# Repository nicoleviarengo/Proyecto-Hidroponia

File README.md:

# Proyecto-Hidroponia
Primera version

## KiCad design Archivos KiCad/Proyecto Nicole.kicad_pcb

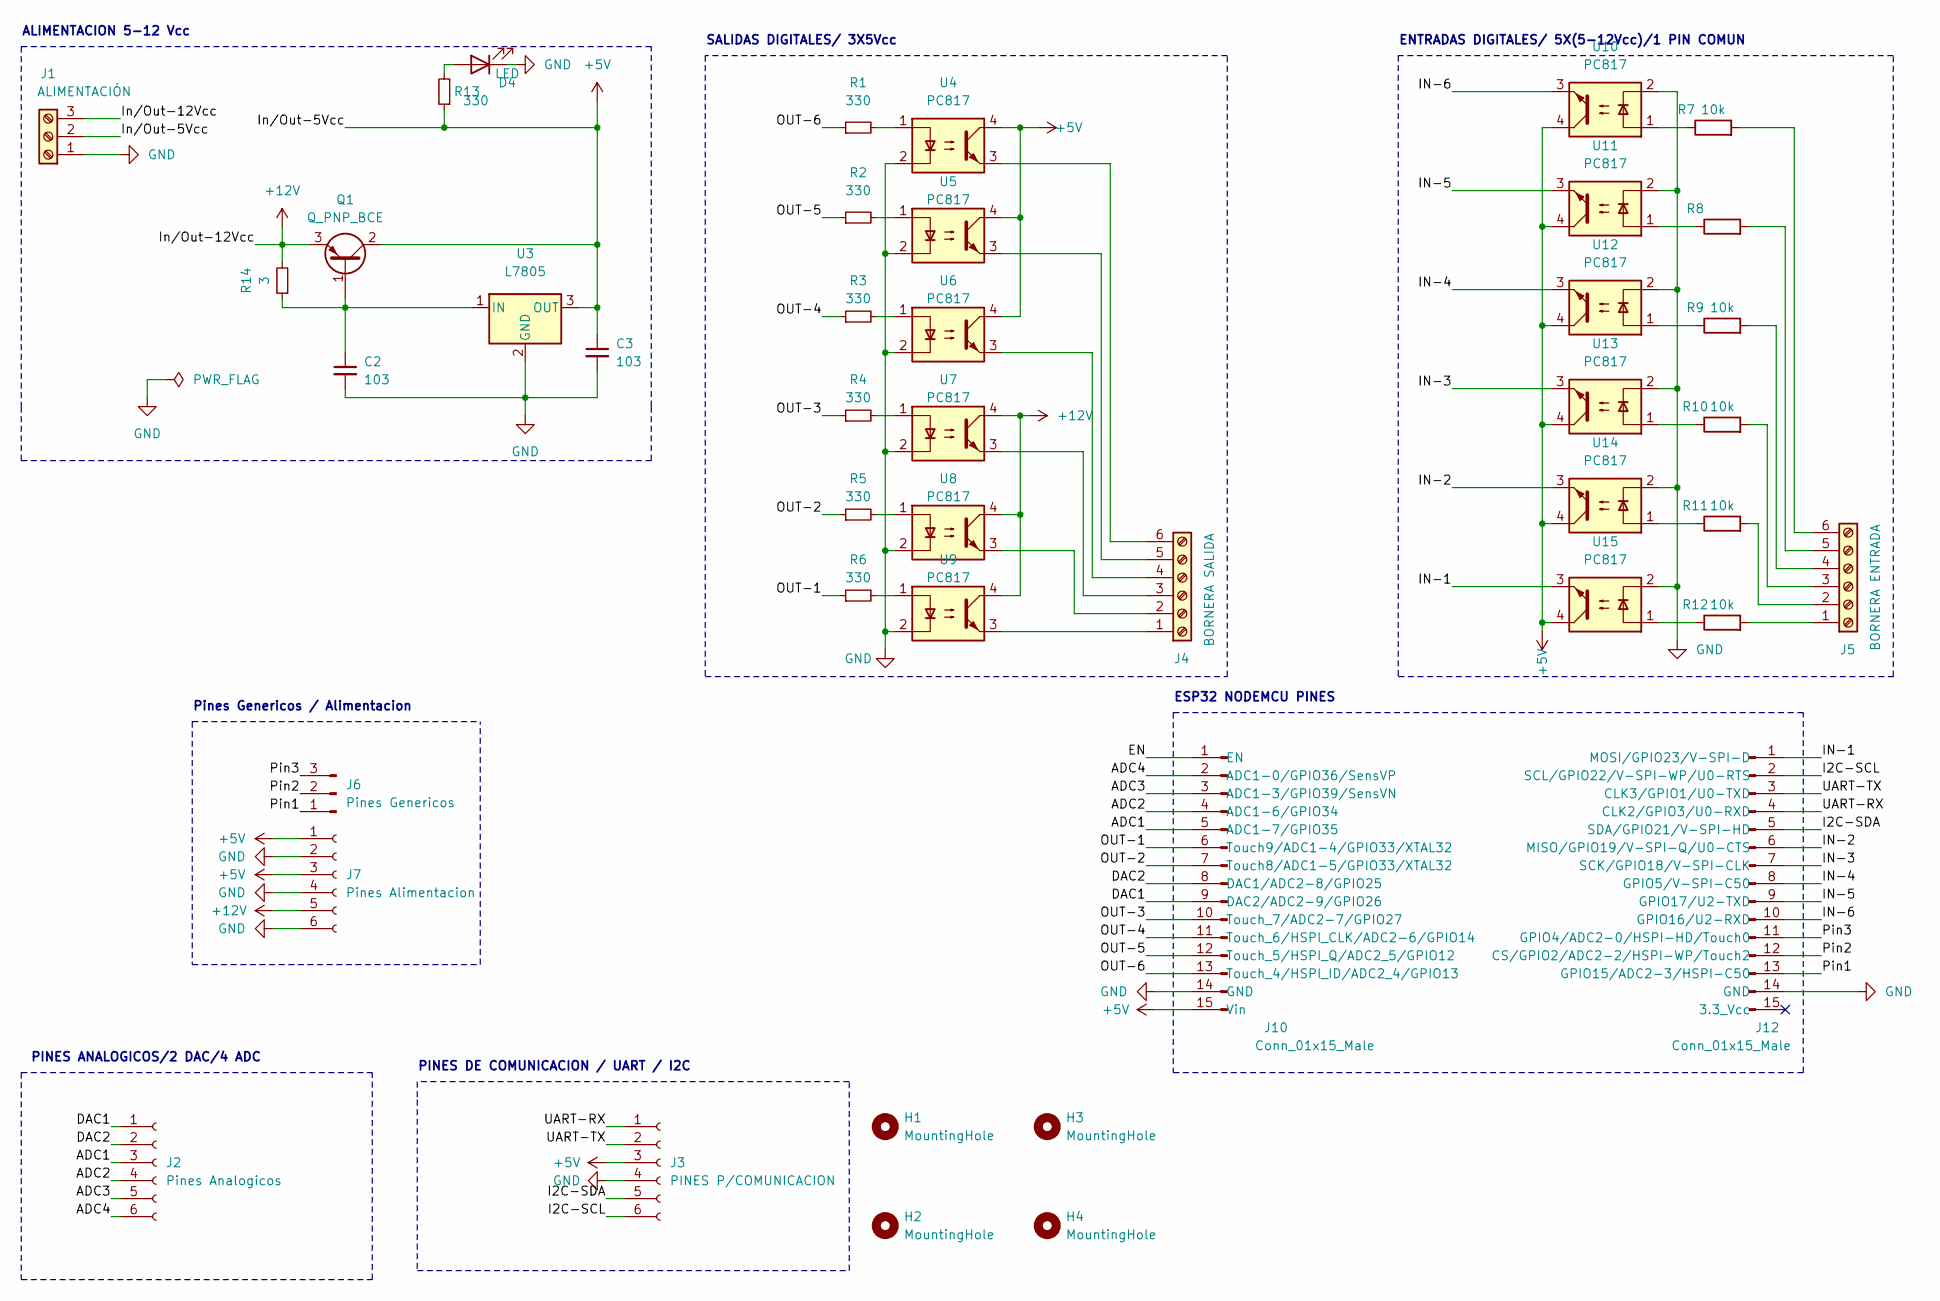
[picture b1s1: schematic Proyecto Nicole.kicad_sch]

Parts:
C2, C3: 103; C_Disc_D4.3mm_W1.9mm_P5.00mm
D4: LED; LED_D4.0mm
H1, H2, H3, H4: MountingHole; MountingHole_2.5mm_Pad
J1: ALIMENTACIÓN; TerminalBlock_Phoenix_MKDS-3-3-5.08_1x03_P5.08mm_Horizontal
J2: Pines Analogicos; PinSocket_1x06_P2.54mm_Vertical
J3: PINES P/COMUNICACION; PinSocket_1x06_P2.54mm_Vertical
J4: BORNERA SALIDA; TerminalBlock_Phoenix_MKDS-3-6-5.08_1x06_P5.08mm_Horizontal
J5: BORNERA ENTRADA; TerminalBlock_Phoenix_MKDS-3-6-5.08_1x06_P5.08mm_Horizontal
J6: Pines Genericos; PinSocket_1x03_P2.54mm_Vertical
J7: Pines Alimentacion; PinSocket_1x06_P2.54mm_Vertical
J10, J12: Conn_01x15_Male; PinSocket_1x15_P2.54mm_Vertical
Q1: Q_PNP_BCE; TO-220-3_Vertical
R1, R2, R3, R4, R5, R6, R13: 330; R_Axial_DIN0207_L6.3mm_D2.5mm_P7.62mm_Horizontal
R7, R8, R9, R10, R11, R12: 10k; R_Axial_DIN0207_L6.3mm_D2.5mm_P7.62mm_Horizontal
R14: 3; R_Axial_DIN0207_L6.3mm_D2.5mm_P7.62mm_Horizontal
U3: L7805; TO-220-3_Vertical
U4, U5, U6, U7, U8, U9, U10, U11, U12, U13, U14, U15: PC817; DIP-4_W7.62mm

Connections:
+5V: C3.1, J1.2, J3.3, J7.1, J7.3, J10.15 (Vin), Q1.2 (C), R13.1, U3.3 (OUT), U4.4, U5.4, U6.4, U10.4, U11.4, U12.4, U13.4, U14.4, U15.4
+12V: J1.3, J7.5, Q1.3 (E), R14.2, U7.4, U8.4, U9.4
/ADC1: J2.3, J10.5 (ADC1-7/GPIO35)
/ADC2: J2.4, J10.4 (ADC1-6/GPIO34)
/ADC3: J2.5, J10.3 (ADC1-3/GPIO39/SensVN)
/ADC4: J2.6, J10.2 (ADC1-0/GPIO36/SensVP)
/DAC1: J2.1, J10.9 (DAC2/ADC2-9/GPIO26)
/DAC2: J2.2, J10.8 (DAC1/ADC2-8/GPIO25)
/EN: J10.1 (EN)
/I2C-SCL: J3.6, J12.2 (SCL/GPIO22/V-SPI-WP/U0-RTS)
/I2C-SDA: J3.5, J12.5 (SDA/GPIO21/V-SPI-HD)
/IN-1: J12.1 (MOSI/GPIO23/V-SPI-D), U15.3
/IN-2: J12.6 (MISO/GPIO19/V-SPI-Q/U0-CTS), U14.3
/IN-3: J12.7 (SCK/GPIO18/V-SPI-CLK), U13.3
/IN-4: J12.8 (GPIO5/V-SPI-C50), U12.3
/IN-5: J12.9 (GPIO17/U2-TXD), U11.3
/IN-6: J12.10 (GPIO16/U2-RXD), U10.3
/OUT-1: J10.6 (Touch9/ADC1-4/GPIO33/XTAL32), R6.1
/OUT-2: J10.7 (Touch8/ADC1-5/GPIO33/XTAL32), R5.1
/OUT-3: J10.10 (Touch_7/ADC2-7/GPIO27), R4.1
/OUT-4: J10.11 (Touch_6/HSPI_CLK/ADC2-6/GPIO14), R3.1
/OUT-5: J10.12 (Touch_5/HSPI_Q/ADC2_5/GPIO12), R2.1
/OUT-6: J10.13 (Touch_4/HSPI_ID/ADC2_4/GPIO13), R1.1
/Pin1: J6.1, J12.13 (GPIO15/ADC2-3/HSPI-C50)
/Pin2: J6.2, J12.12 (CS/GPIO2/ADC2-2/HSPI-WP/Touch2)
/Pin3: J6.3, J12.11 (GPIO4/ADC2-0/HSPI-HD/Touch0)
/UART-RX: J3.1, J12.4 (CLK2/GPIO3/U0-RXD)
/UART-TX: J3.2, J12.3 (CLK3/GPIO1/U0-TXD)
GND: C2.2, C3.2, D4.1 (K), J1.1, J3.4, J7.2, J7.4, J7.6, J10.14 (GND), J12.14 (GND), U3.2 (GND), U4.2, U5.2, U6.2, U7.2, U8.2, U9.2, U10.2, U11.2, U12.2, U13.2, U14.2, U15.2
unnamed: D4.2 (A), R13.2
unnamed: J4.1, U9.3
unnamed: J4.2, U8.3
unnamed: J4.3, U7.3
unnamed: J4.4, U6.3
unnamed: J4.5, U5.3
unnamed: J4.6, U4.3
unnamed: J5.1, R12.2
unnamed: J5.2, R11.2
unnamed: J5.3, R10.2
unnamed: J5.4, R9.2
unnamed: J5.5, R8.2
unnamed: J5.6, R7.2
unnamed: C2.1, Q1.1 (B), R14.1, U3.1 (IN)
unnamed: R1.2, U4.1
unnamed: R2.2, U5.1
unnamed: R3.2, U6.1
unnamed: R4.2, U7.1
unnamed: R5.2, U8.1
unnamed: R6.2, U9.1
unnamed: R7.1, U10.1
unnamed: R8.1, U11.1
unnamed: R9.1, U12.1
unnamed: R10.1, U13.1
unnamed: R11.1, U14.1
unnamed: R12.1, U15.1

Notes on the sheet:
PINES DE COMUNICACION / UART / I2C
SALIDAS DIGITALES/ 3X5Vcc
ALIMENTACION 5-12 Vcc
ENTRADAS DIGITALES/ 5X(5-12Vcc)/1 PIN COMUN
PINES ANALOGICOS/2 DAC/4 ADC
ESP32 NODEMCU PINES
Pines Genericos / Alimentacion

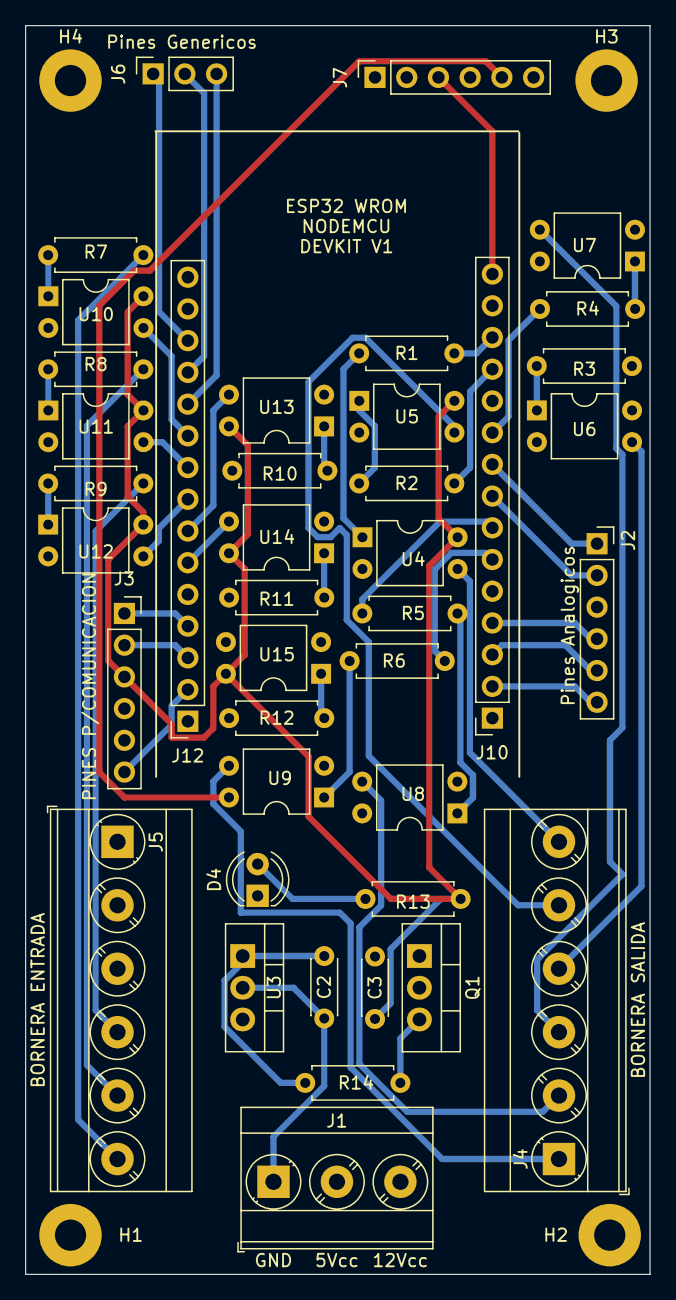
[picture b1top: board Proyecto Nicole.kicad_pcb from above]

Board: 2 copper layers, 50.0 x 100.0 mm, 44 parts (0 on the bottom side), 54 nets.

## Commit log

2024-09-09 Presentacion del funcionamiento
2024-09-09 maceta en 3d
2024-12-10 Diseño de la placa
2024-12-10 Programa en Arduino
2024-12-10 Imagen
2024-12-10 Informe del proyecto
2024-12-10 Sistema
